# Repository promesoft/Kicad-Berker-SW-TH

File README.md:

Green board

# Overview
## Status - Rev A - Functional with issues
Rev A done by PCBWay

## Wemos D1 mini - section 1

Section 1 is a sensor board for a Wemos D1 mini, that is intended for installing in a Berker wall outlet (euro style). 
Section 1 has an AM2320, a relay and a power supply. Besides this it has breakout of pins A0 and D4.

## Issues

There is one issue with section 1 that should be addressed in the next revision. The board size is 2mm too big in X and Y, to fit into a Berker wall mount. 

## Errata
 - Edgecuts in Rev A is specified as 0,15mm - this should be 1mm
 - Footprint for AC-DC is wrong
 - Footprint for Q3 and Q4 is off

## Wemos D1 mini - section 2

Section 2 is similar to section 1 except it has room on the backside for a PM03 AC-DC converter. 
It is intended as a board for installing in a Berker outlet. 
Section 2 has an AM2320, a relay and a power supply. Besides this it has breakout of pins A0 and D4.

## Issues

There are two flaws with section 2 that should be addressed in the next revision: 
### Board dimensions
The corners of the board inhibits it from fitting into a Berker wall mount. 
Either the board should be 47x47mm (3mm shorter in X and Y) or the corners should be milled away with a 8mm diameter drill
### Footprint of AC-DC converter
The PM03 footprint has been flipped so it does not fit in the PCB.

## Virtual Ground Section

# 3D board view

# Shecmatic

# Section 2

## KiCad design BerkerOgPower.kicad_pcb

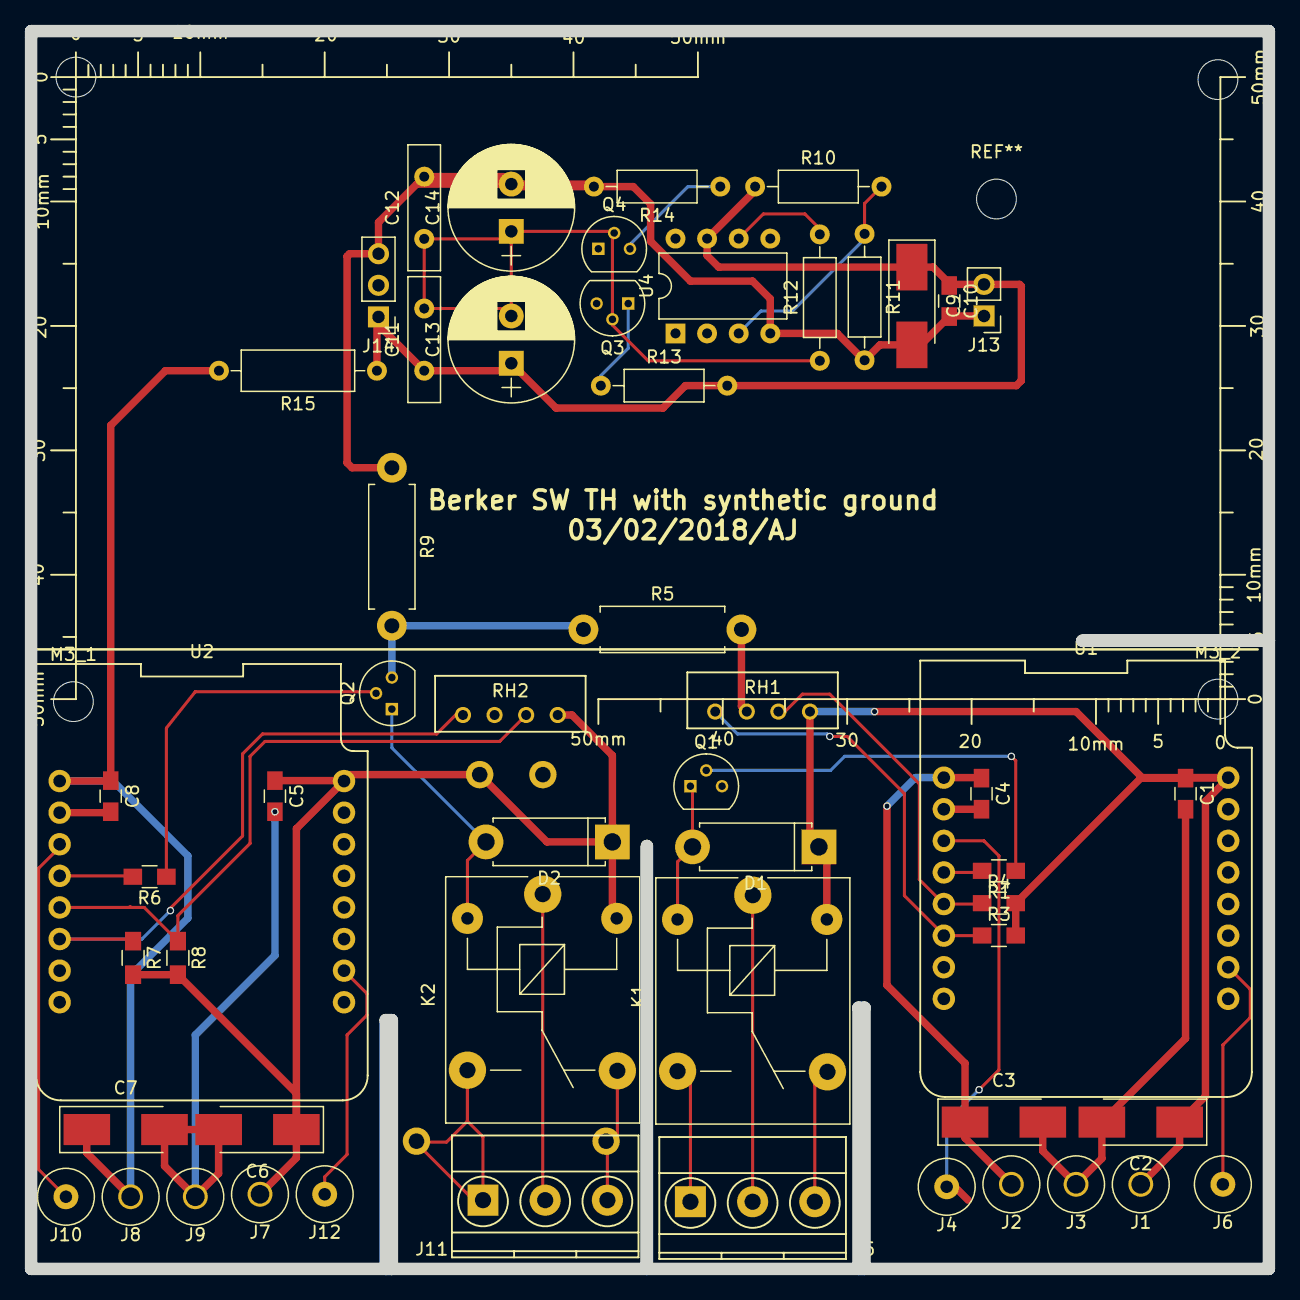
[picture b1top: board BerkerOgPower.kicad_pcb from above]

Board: 2 copper layers, 99.5 x 99.5 mm, 58 parts (1 on the bottom side), 34 nets.

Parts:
C1, C4, C5, C8, C10: 100n; C_0805_HandSoldering
C2, C3, C6, C7, C9: 100uF; CP_Tantalum_Case-C_EIA-6032-28_Hand
C11, C12: 100nF; C_Disc_D10.0mm_W2.5mm_P5.00mm
C13, C14: 100uF; CP_Radial_D10.0mm_P3.80mm
D1, D2: D; D_5W_P10.16mm_Horizontal
J1: +3,31V; 1pin
J2: +5.1V; 1pin
J3, J9: GND; 1pin
J4, J10: D4; 1pin
J5, J11: Screw_Terminal_01x03; TerminalBlock_Phoenix_MKDS1.5-3pol
J6, J12: A0; 1pin
J7: +3,32V; 1pin
J8: +5.2V; 1pin
J13: Conn_01x02; Pin_Header_Straight_1x02_Pitch2.54mm
J14: Conn_01x03; Pin_Header_Straight_1x03_Pitch2.54mm
K1, K2: SANYOU_SRD_Form_C; Relay_SPDT_SANYOU_SRD_Series_Form_C
M3_1, M3_2: MountingHole_3.2mm_M3_DIN965
Q1: BC547; TO-92_Molded_Narrow
Q2: BC337; TO-92_Molded_Narrow
Q3: BC338; TO-92_Molded_Narrow
Q4: BC328; TO-92_Molded_Narrow
R1, R3, R4, R6, R7, R8: 10k; R_0805_HandSoldering
R5: GNDD; R_Axial_DIN0411_L9.9mm_D3.6mm_P12.70mm_Horizontal
R9: GNDA; R_Axial_DIN0411_L9.9mm_D3.6mm_P12.70mm_Horizontal
R10, R11: 220R; R_Axial_DIN0207_L6.3mm_D2.5mm_P10.16mm_Horizontal
R12: 1k; R_Axial_DIN0207_L6.3mm_D2.5mm_P10.16mm_Horizontal
R13, R14: 10R; R_Axial_DIN0207_L6.3mm_D2.5mm_P10.16mm_Horizontal
R15: +5C; R_Axial_DIN0309_L9.0mm_D3.2mm_P12.70mm_Horizontal
RH1, RH2: AM2320
U1, U2: WeMos_mini; wemos-d1-mini-connectors-only
U3: HLK-PM03; HLK-PM03-AJ
U4: TL071; DIP-8_W7.62mm

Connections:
+3.3VA: C5.1, C6.1, D2.1, J7.1, K2.5, R7.2, R8.2, RH2.1, U2.16, U3.4
+3V3: C1.1, C2.1, D1.1, J1.1, K1.5, R3.2, R4.2, RH1.1, U1.16
+5C: C7.1, C8.1, J8.1, R15.2, U2.1
+5VD: C3.1, C4.1, J2.1, U1.1
+12VA: C9.1, C10.1, C11.1, C13.1, J13.2, J14.1, R10.1, R13.2, R15.1, U4.7
GND: C5.2, C6.2, C7.2, C8.2, J9.1, Q2.3, R5.1, R9.2, RH2.3, U2.2, U3.3
GNDA: J14.2, Q3.3, Q4.1, U4.2
GNDD: C1.2, C2.2, C3.2, C4.2, J3.1, Q1.3, R5.2, RH1.3, U1.2
GNDPWR: C9.2, C10.2, C12.2, C14.2, J13.1, J14.3, R9.1, R11.2, R14.2, U4.4
unnamed: C11.2, C12.1, C13.2, C14.1, Q3.2, Q4.2, R12.1
unnamed: D1.2, K1.2, Q1.1
unnamed: D2.2, K2.2, Q2.1
unnamed: J4.1, U1.3
unnamed: J5.1, K1.3
unnamed: J5.2, K1.1
unnamed: J5.3, K1.4
unnamed: J6.1, U1.10
unnamed: J10.1, U2.3
unnamed: J11.1, K2.3, U3.2
unnamed: J11.2, K2.1
unnamed: J11.3, K2.4, U3.1
unnamed: J12.1, U2.10
unnamed: Q1.2, R1.1
unnamed: Q2.2, R6.1
unnamed: Q3.1, R13.1
unnamed: Q4.3, R14.1
unnamed: R1.2, U1.4
unnamed: R3.1, RH1.4, U1.6
unnamed: R4.1, RH1.2, U1.5
unnamed: R6.2, U2.4
unnamed: R7.1, RH2.4, U2.6
unnamed: R8.1, RH2.2, U2.5
unnamed: R10.2, R11.1, U4.3
unnamed: R12.2, U4.6

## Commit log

2018-12-18 Create README.md
    init
2018-12-18 Project restore
    Restored from local copy
2018-12-18 Create Kicad-Berker-2-Wemos-Sch.png
    schematic
2018-12-18 Create Kicad-Berker-2-Wemos-3D.png
    3D pict
2018-12-19 Update README.md
    3D
2018-12-20 Update README.md
    sch upload
2018-12-20 Update README.md
    fix view
2018-12-21 Update README.md
    section 1
2019-01-15 3D and edgecut
